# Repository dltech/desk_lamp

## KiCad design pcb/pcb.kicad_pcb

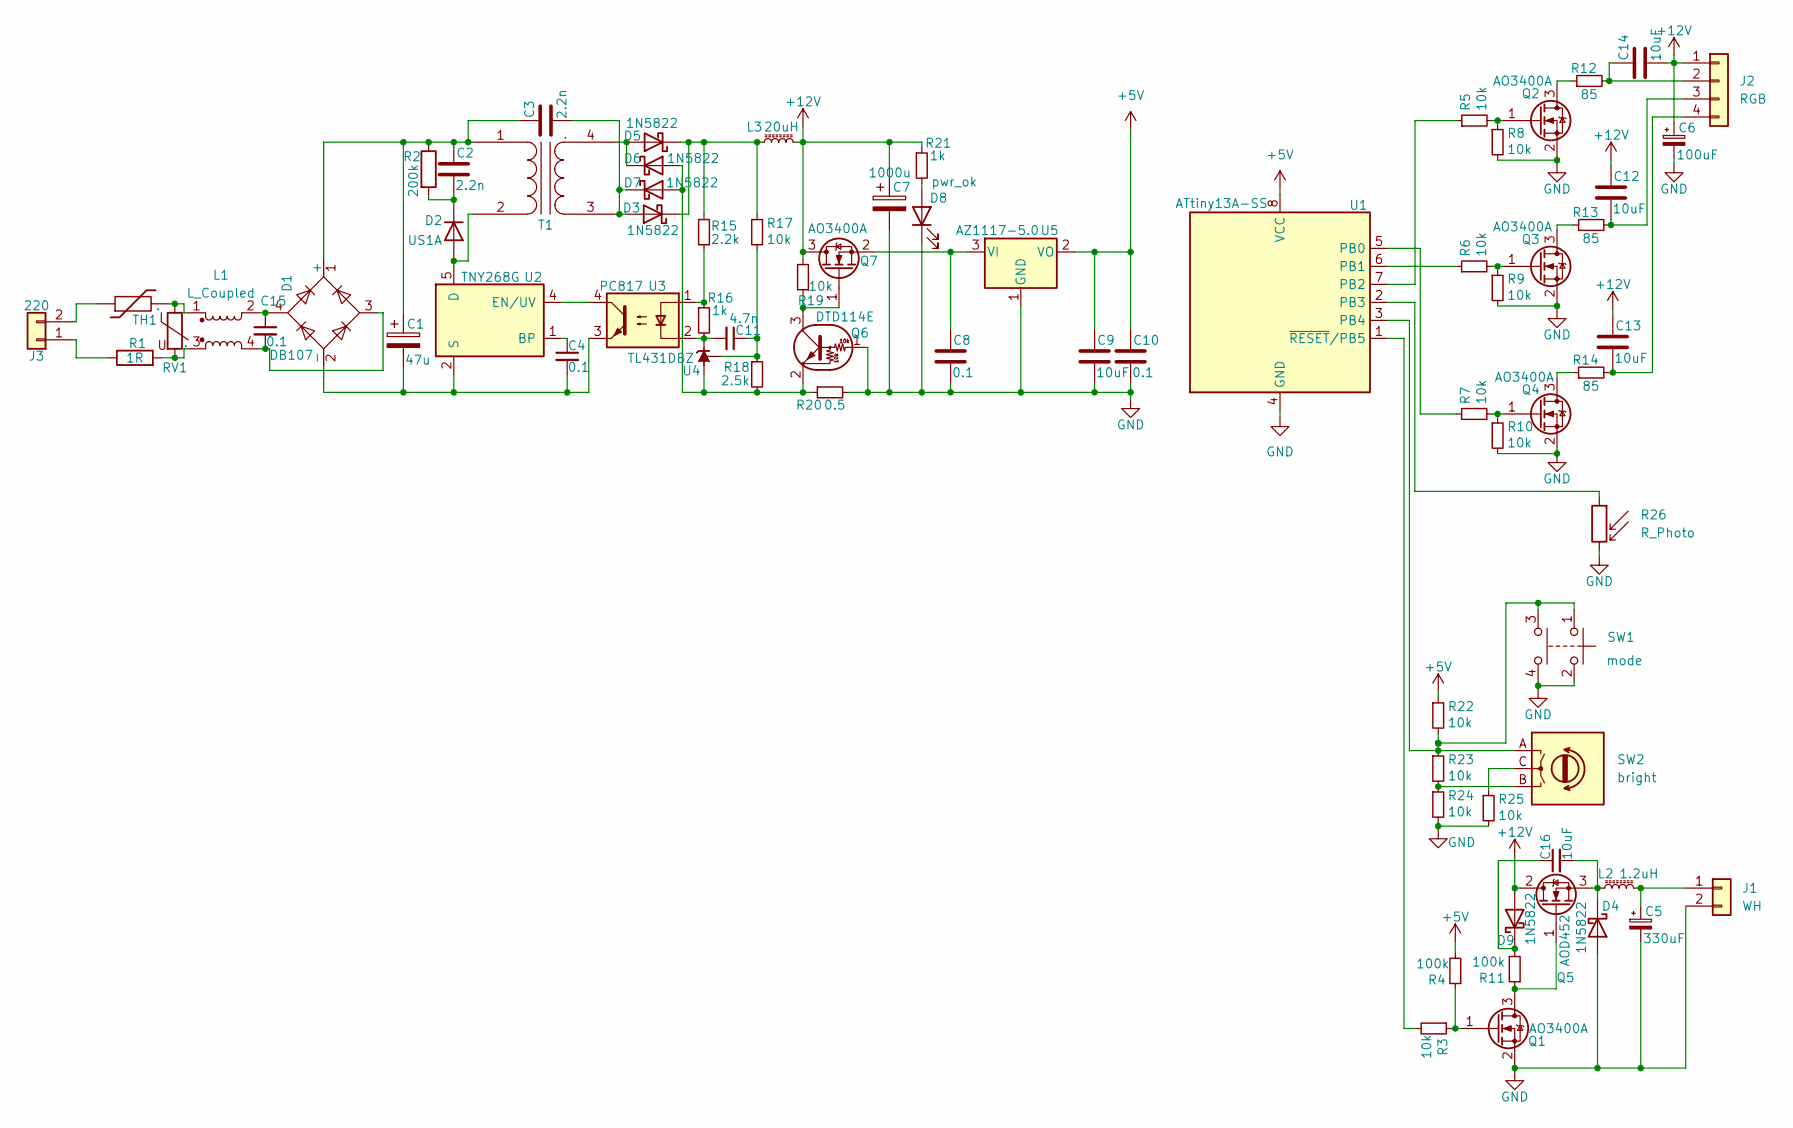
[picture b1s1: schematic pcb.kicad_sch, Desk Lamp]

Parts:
C1: 47u; CP_Radial_D10.0mm_P7.50mm
C2, C3: 2.2n; C_Axial_L3.8mm_D2.6mm_P7.50mm_Horizontal
C4: 0.1; C_0805_2012Metric
C5: 330uF; CP_Radial_D10.0mm_P5.00mm
C6: 100uF; CP_Elec_6.3x7.7
C7: 1000u; CP_Radial_D10.0mm_P5.00mm
C8, C10: 0.1; C_0402_1005Metric
C9, C12, C13, C14, C16: 10uF; C_0805_2012Metric
C11: 4.7n; C_0402_1005Metric
C15: 0.1; C_Disc_D11.0mm_W5.0mm_P10.00mm
D1: DB107; Diode_Bridge_OnSemi_SDIP-4L
D2: US1A; D_SMA
D3, D4, D5, D6, D7: 1N5822; D_SMA
D8: pwr_ok; LED_0603_1608Metric
D9: 1N5822; D_SOD-323
J1: WH; PinHeader_1x02_P2.54mm_Vertical
J2: RGB; PinHeader_1x04_P2.54mm_Vertical
J3: 220; SolderWire-0.1sqmm_1x02_P3.6mm_D0.4mm_OD1mm
L1: L_Coupled; Input_coil
L2: 1.2uH; L_Radial_D12.0mm_P10.00mm_Neosid_SD12k_style1
L3: 20uH; L_Radial_D16.8mm_P11.43mm_Vishay_IHB-1
Q1, Q2, Q3, Q4, Q7: AO3400A; SOT-23
Q5: AOD452; TO-252-2
Q6: DTD114E; SOT-23
R1: 1R; R_1210_3225Metric
R2: 200k; R_1210_3225Metric
R3, R5, R6, R7, R8, R9, R10, R17, R19, R22, R23, R24, R25: 10k; R_0402_1005Metric
R4, R11: 100k; R_0402_1005Metric
R12, R13, R14: 85; R_1206_3216Metric
R15: 2.2k; R_0402_1005Metric
R16, R21: 1k; R_0402_1005Metric
R18: 2.5k; R_0805_2012Metric
R20: 0.5; R_1210_3225Metric
R26: R_Photo; LED_D3.0mm
RV1: .; RV_Disc_D12mm_W3.9mm_P7.5mm
SW1: mode; SW_PUSH_6mm_2cont
SW2: bright; mouse_encoder
T1: .; Transformer_NF_ETAL_P1165
TH1: .; RV_Disc_D12mm_W3.9mm_P7.5mm
U1: ATtiny13A-SS; SOIC-8_3.9x4.9mm_P1.27mm
U2: TNY268G; PowerIntegrations_SMD-8B
U3: PC817; SOP-4_3.8x4.1mm_P2.54mm
U4: TL431DBZ; SOT-23
U5: AZ1117-5.0; SOT-223

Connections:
+5V: C9.1, C10.1, R4.2, R22.1, U1.8 (VCC), U5.2 (VO)
+12V: C6.1, C7.1, C12.1, C13.1, C14.2, D9.2 (A), J2.1, L3.2, Q5.2 (D), Q7.3 (D), R19.2, R21.1
GND: C5.2, C6.2, C7.2, C8.2, C9.2, C10.2, D4.2 (A), D8.1 (K), J1.2, Q1.2 (S), Q2.2 (S), Q3.2 (S), Q4.2 (S), Q6.1 (B), R8.2, R9.2, R10.2, R20.2, R24.2, R25.2, R26.2, SW1.2, SW1.4, U1.4 (GND), U5.1 (GND)
unnamed: C1.1, C2.1, C3.1, D1.1 (+), R2.1, T1.1 (AA)
unnamed: C1.2, C4.2, D1.2 (-), U2.2 (S), U2.3 (S), U2.7 (S), U2.8 (S), U3.3
unnamed: C2.2, D2.1 (K), R2.2
unnamed: C3.2, D3.2 (A), D7.1 (K), T1.3 (SA)
unnamed: C4.1, U2.1 (BP)
unnamed: C5.1, J1.1, L2.2
unnamed: C8.1, Q7.2 (S), U5.3 (VI)
unnamed: C11.1, R17.2, R18.1, U4.2 (REF)
unnamed: C11.2, R16.2, U3.2, U4.1 (K)
unnamed: C12.2, J2.3, R13.2
unnamed: C13.2, J2.4, R14.2
unnamed: C14.1, J2.2, R12.2
unnamed: C15.1, D1.4, L1.2
unnamed: C15.2, D1.3, L1.4
unnamed: D2.2 (A), T1.2 (AB), U2.5 (D)
unnamed: D3.1 (K), D5.1 (K), L3.1, R15.1, R17.1
unnamed: C16.2, D4.1 (K), L2.1, Q5.3 (S)
unnamed: D5.2 (A), D6.1 (K), T1.4 (SB)
unnamed: D6.2 (A), D7.2 (A), Q6.2 (E), R18.2, R20.1, U4.3 (A)
unnamed: D8.2 (A), R21.2
unnamed: J3.1, R1.1
unnamed: J3.2, TH1.1
unnamed: L1.1, RV1.1, TH1.2
unnamed: L1.3, R1.2, RV1.2
unnamed: Q1.1 (G), R3.1, R4.1
unnamed: Q1.3 (D), Q5.1 (G), R11.1
unnamed: Q2.1 (G), R5.2, R8.1
unnamed: Q2.3 (D), R12.1
unnamed: Q3.1 (G), R6.2, R9.1
unnamed: Q3.3 (D), R13.1
unnamed: Q4.1 (G), R7.2, R10.1
unnamed: Q4.3 (D), R14.1
unnamed: Q6.3 (C), Q7.1 (G), R19.1
unnamed: R3.2, U1.1 (~RESET/PB5)
unnamed: R5.1, U1.7 (PB2)
unnamed: R6.1, U1.6 (PB1)
unnamed: R7.1, U1.5 (PB0)
unnamed: C16.1, D9.1 (K), R11.2
unnamed: R15.2, R16.1, U3.1
unnamed: R22.2, R23.1, SW1.1, SW1.3, SW2.A, U1.3 (PB4)
unnamed: R23.2, R24.1, SW2.B
unnamed: R25.1, SW2.C
unnamed: R26.1, U1.2 (PB3)
unnamed: U2.4 (EN/UV), U3.4

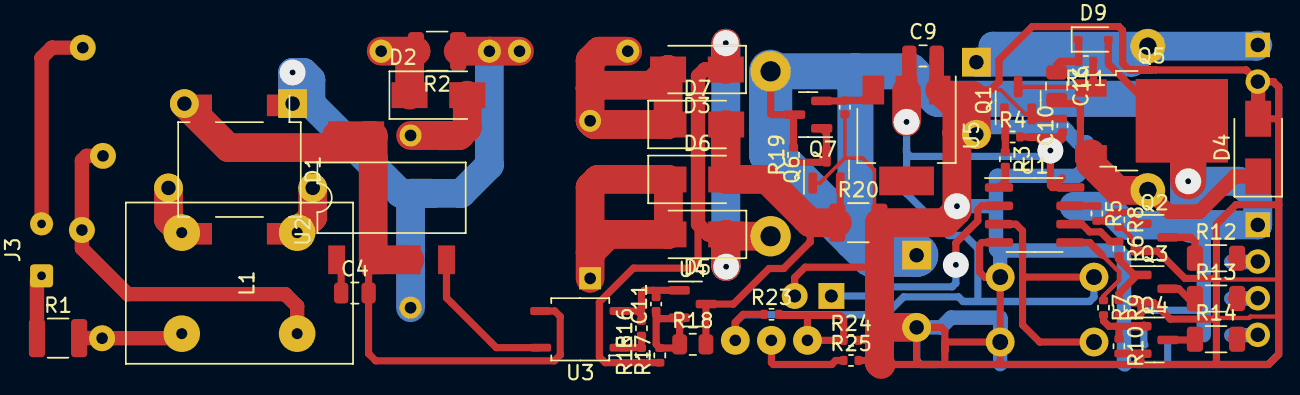
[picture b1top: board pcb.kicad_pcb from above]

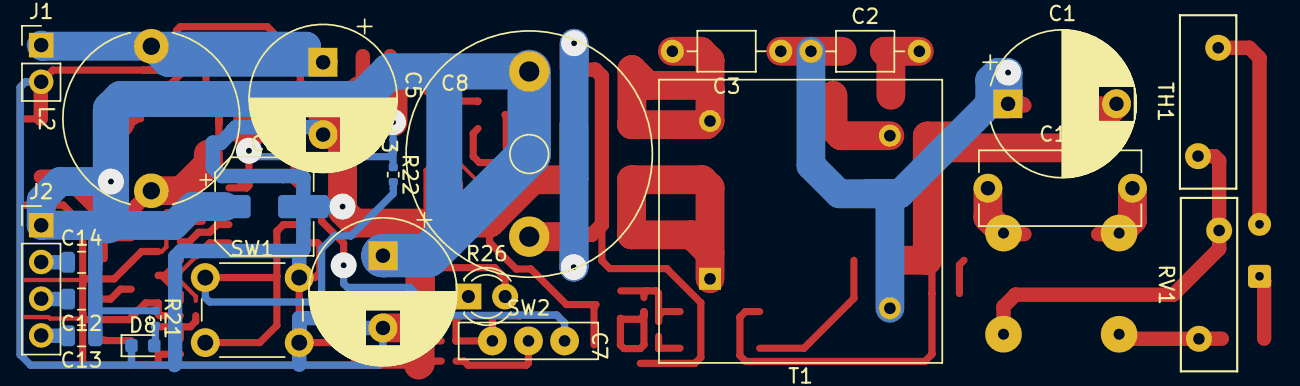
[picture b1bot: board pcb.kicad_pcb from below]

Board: 2 copper layers, 74 parts (23 on the bottom side), 47 nets.

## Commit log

2022-06-17 lamp schematic
2022-06-17 err in sch
2022-06-21 short circuit protection
2022-06-23 pcb fottprints ok, layout tomorrow
2022-06-24 pcb ok, code is coming
2022-06-27 operate led
2022-06-27 -2cm
2022-07-05 err in sch, some code added
2022-07-06 8-bits random, adc regs
2022-07-07 fw compiled, 200kb need to optimise
2022-07-07 optimized + watchdog registers
2022-07-10 lamp on sch
2022-07-10 light sensor added completely
2022-07-11 -0.5 cm
2022-07-15 mosfet bootstrap circuit
